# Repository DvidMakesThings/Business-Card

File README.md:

# Business_Card_LA Project

Business_Card_LA is a unique project where a business card doubles as a logic analyzer. It is designed based on Cypress CY7C68013A USB controller. It can sample 8 channels at the same time. The maximum sampling rate of each channel is 24Mhz, and the maximum logical level supports 5.5V. The software adopts sigrok-PulseView, which is open source, and supports Linux, Windows, Mac OS X and other platforms. It supports more than 100 kinds of protocol analysis, and can add its own protocol analysis.

## Specifications
- **Sampling rate and number of channels**: 24Mhz, 8 Channel
- **Signal input range**: 0-5.5V
- **High and low level recognition range**: Vin High: >2V, Vin Low: <0.8V
- **Communication mode**: USB 2.0 (In order to ensure the sampling rate of 24Mhz, try not to use USB docking station)

## Usage
1. **Download sigrok-PulseView Software**: Be sure to download the Release build from [sigrok Downloads](https://sigrok.org/wiki/Downloads).
2. **Install sigrok-PulseView & LogicAnalyzer driver**:
   - After PulseView is installed, run Zadig from the installation folder: `\sigrok\PulseView\zadig.exe`.
   - Select the device you want to install the driver on. The business card appears as Unknown device with VID/PID 04B4:8613.
   - Check Edit, change the device name to fx2LAFw, and then click Install Driver.
3. **Run PulseView**:
   - Click PulseView to run the software.
   - The status LED will light up and it's blue, indicating that the firmware is loaded successfully and the logic signal can be sampled.

## Supported Protocols
See [sigrok Supported Protocol decoders](https://sigrok.org/wiki/Protocol_decoders).

## License
This project is licensed under the GPL-3.0 License.

## Contact
For any questions or feedback, please contact:
- Email: [s.dvid@hotmail.com](mailto:s.dvid@hotmail.com)
- GitHub: [DvidMakesThings](https://github.com/DvidMakesThings)

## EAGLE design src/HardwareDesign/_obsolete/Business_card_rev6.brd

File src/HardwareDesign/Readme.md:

# # Business_Card_LA Project Hardware Design Files

## Contents
This folder contains the hardware design files for the Business_Card_LA project. The main components include:
- Schematic diagrams
- PCB layouts
- Bill of Materials (BOM)
- Gerber files

## Usage
To use these hardware design files:
1. Open the schematic diagrams and PCB layouts using EAGLE software.
2. Review the Bill of Materials for required components.
3. Follow the design files to assemble and test the hardware.
4. Use the Gerber files for PCB manufacturing.

## License
This project is licensed under the MIT License.

## Contact
For any questions or feedback, please contact:
- Email: [s.dvid@hotmail.com](mailto:s.dvid@hotmail.com)
- GitHub: [DvidMakesThings](https://github.com/DvidMakesThings)

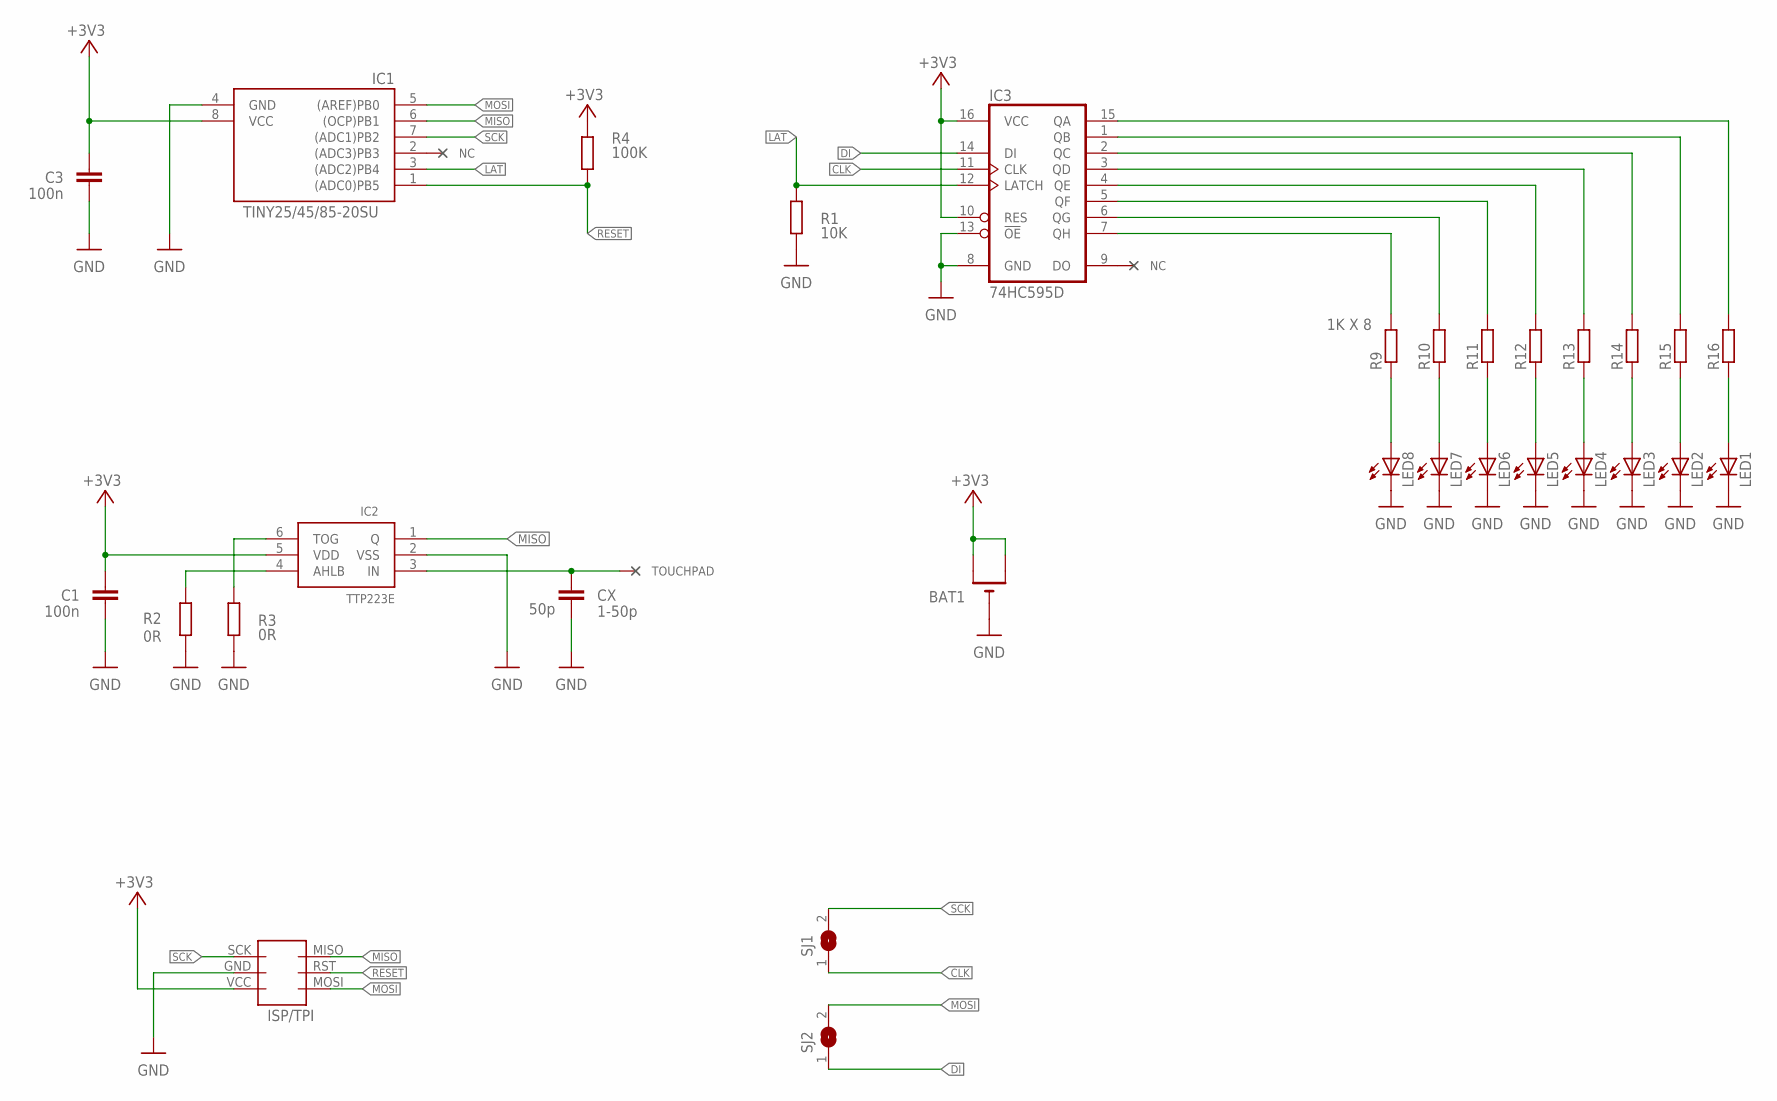
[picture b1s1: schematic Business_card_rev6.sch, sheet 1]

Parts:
BAT1: CR2032SMT; CR2032-SMD
C1, C3: 100n; C1206K
CX: 1-50p; C1206K
IC1: TINY25/45/85-20SU; SOIC8
IC2: TTP223E; SOT23-6
IC3: 74HC595D; SO16
LED1, LED2, LED3, LED4, LED5, LED6, LED7, LED8: LEDCHIPLED_0805; CHIPLED_0805
R1: 10K; M0805
R2, R3: 0R; M0805
R4: 100K; M0805
R9, R10, R11, R12, R13, R14, R15, R16: R-EU_M0805; M0805
SJ1, SJ2: SJ
U$11: AVR-ISP-6-EDGE; 6PAD_ISP

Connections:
+3V3: BAT1.+$1 (+), BAT1.+$2 (+1), C1.2, C3.2, IC1.8 (VCC), IC2.5 (VDD), IC3.10 (RES), IC3.16 (VCC), R4.2, U$11.VCC; also elsewhere on the board
CAPSEN: CX.2, IC2.3 (IN)
CLK: IC3.11 (CLK), SJ1.1
DI: IC3.14 (DI), SJ2.1
GND: BAT1.-, C1.1, C3.1, CX.1, IC1.4 (GND), IC2.2 (VSS), IC3.8 (GND), IC3.13 (!OE), LED1.C, LED2.C, LED3.C, LED4.C, LED5.C, LED6.C, LED7.C, LED8.C, R1.2, R2.1, R3.1, U$11.GND; also elsewhere on the board
LAT: IC1.3 ((ADC2)PB4), IC3.12 (LATCH), R1.1
MISO: IC1.6 ((OCP)PB1), IC2.1 (Q), U$11.MISO
MOSI: IC1.5 ((AREF)PB0), SJ2.2, U$11.MOSI
unnamed: IC3.15 (QA), R16.2
unnamed: IC3.1 (QB), R15.2
unnamed: IC2.6 (TOG), R3.2
unnamed: IC2.4 (AHLB), R2.2
unnamed: IC3.2 (QC), R14.2
unnamed: IC3.3 (QD), R13.2
unnamed: IC3.4 (QE), R12.2
unnamed: IC3.5 (QF), R11.2
unnamed: IC3.6 (QG), R10.2
unnamed: IC3.7 (QH), R9.2
unnamed: LED8.A, R9.1
unnamed: LED7.A, R10.1
unnamed: LED6.A, R11.1
unnamed: LED5.A, R12.1
unnamed: LED4.A, R13.1
unnamed: LED3.A, R14.1
unnamed: LED2.A, R15.1
unnamed: LED1.A, R16.1
RESET: IC1.1 ((ADC0)PB5), R4.1, U$11.RST
SCK: IC1.7 ((ADC1)PB2), SJ1.2, U$11.SCK

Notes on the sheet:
50p
TOUCHPAD
IC2
TTP223E
1K X 8

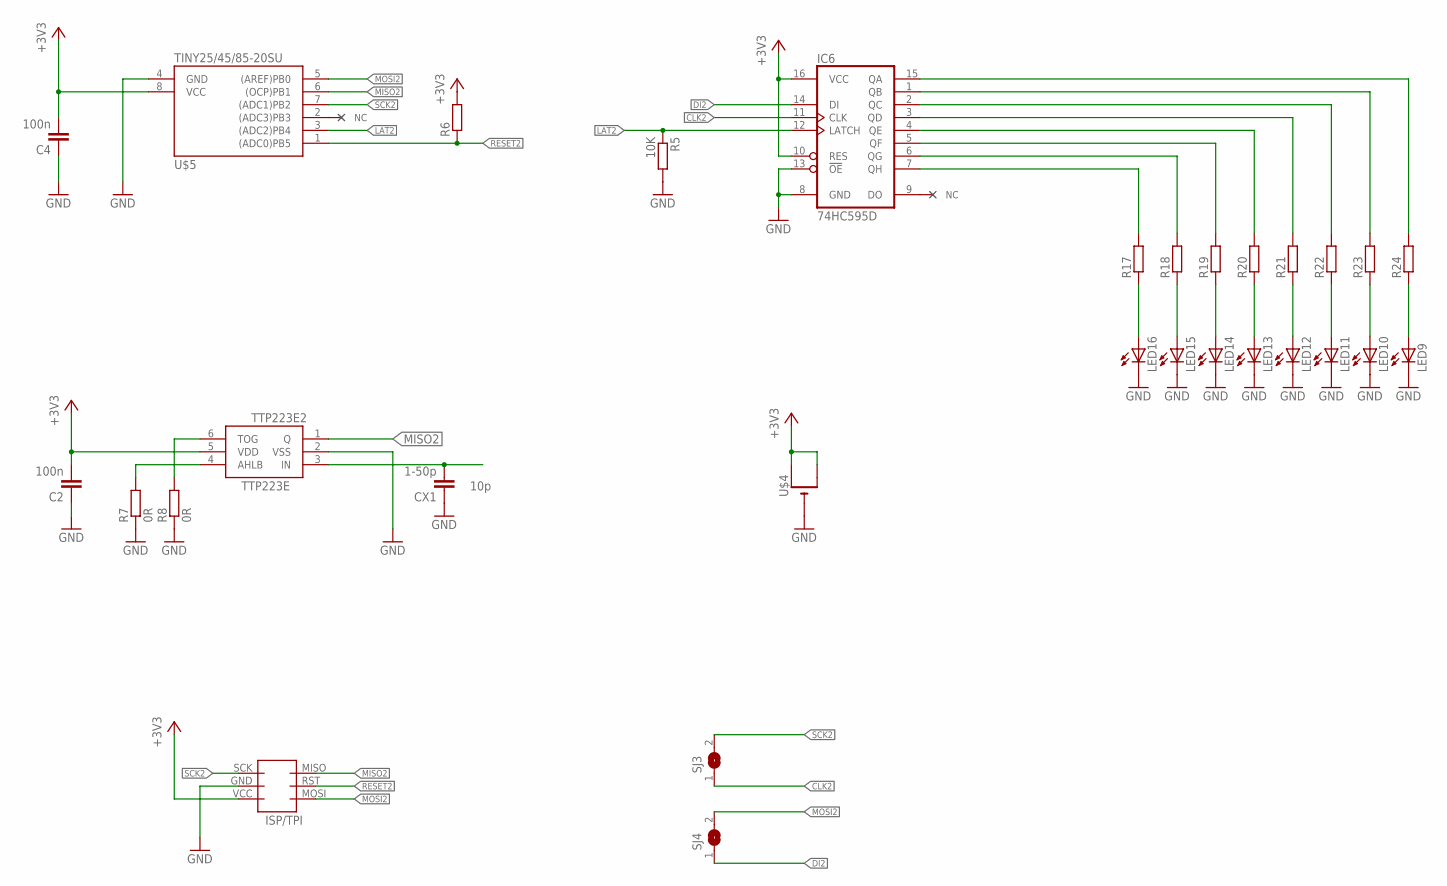
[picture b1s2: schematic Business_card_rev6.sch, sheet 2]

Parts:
C2, C4: 100n; C1206K
CX1: 1-50p; C1206K
IC6: 74HC595D; SO16
LED9, LED10, LED11, LED12, LED13, LED14, LED15, LED16: LEDCHIPLED_0805; CHIPLED_0805
R5: 10K; M0805
R6, R17, R18, R19, R20, R21, R22, R23, R24: R-EU_M0805; M0805
R7, R8: 0R; M0805
SJ3, SJ4: SJ
TTP223E2: TTP223E; SOT23-6
U$4: CR2032SMT; CR2032-SMD
U$5: TINY25/45/85-20SU; SOIC8
U$12: AVR-ISP-6-EDGE; 6PAD_ISP

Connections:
+3V3: C2.2, C4.2, IC6.10 (RES), IC6.16 (VCC), R6.2, TTP223E2.5 (VDD), U$4.+$1 (+), U$4.+$2 (+1), U$5.8 (VCC), U$12.VCC; also elsewhere on the board
CAPSEN1: CX1.2, TTP223E2.3 (IN)
CLK2: IC6.11 (CLK), SJ3.1
DI2: IC6.14 (DI), SJ4.1
GND: C2.1, C4.1, CX1.1, IC6.8 (GND), IC6.13 (!OE), LED9.C, LED10.C, LED11.C, LED12.C, LED13.C, LED14.C, LED15.C, LED16.C, R5.2, R7.1, R8.1, TTP223E2.2 (VSS), U$4.-, U$5.4 (GND), U$12.GND; also elsewhere on the board
LAT2: IC6.12 (LATCH), R5.1, U$5.3 ((ADC2)PB4)
MISO2: TTP223E2.1 (Q), U$5.6 ((OCP)PB1), U$12.MISO
MOSI2: SJ4.2, U$5.5 ((AREF)PB0), U$12.MOSI
unnamed: R8.2, TTP223E2.6 (TOG)
unnamed: R7.2, TTP223E2.4 (AHLB)
unnamed: IC6.15 (QA), R24.2
unnamed: IC6.1 (QB), R23.2
unnamed: IC6.2 (QC), R22.2
unnamed: IC6.3 (QD), R21.2
unnamed: IC6.4 (QE), R20.2
unnamed: IC6.5 (QF), R19.2
unnamed: IC6.6 (QG), R18.2
unnamed: IC6.7 (QH), R17.2
unnamed: LED16.A, R17.1
unnamed: LED15.A, R18.1
unnamed: LED14.A, R19.1
unnamed: LED13.A, R20.1
unnamed: LED12.A, R21.1
unnamed: LED11.A, R22.1
unnamed: LED10.A, R23.1
unnamed: LED9.A, R24.1
RESET2: R6.1, U$5.1 ((ADC0)PB5), U$12.RST
SCK2: SJ3.2, U$5.7 ((ADC1)PB2), U$12.SCK

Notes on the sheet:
10p

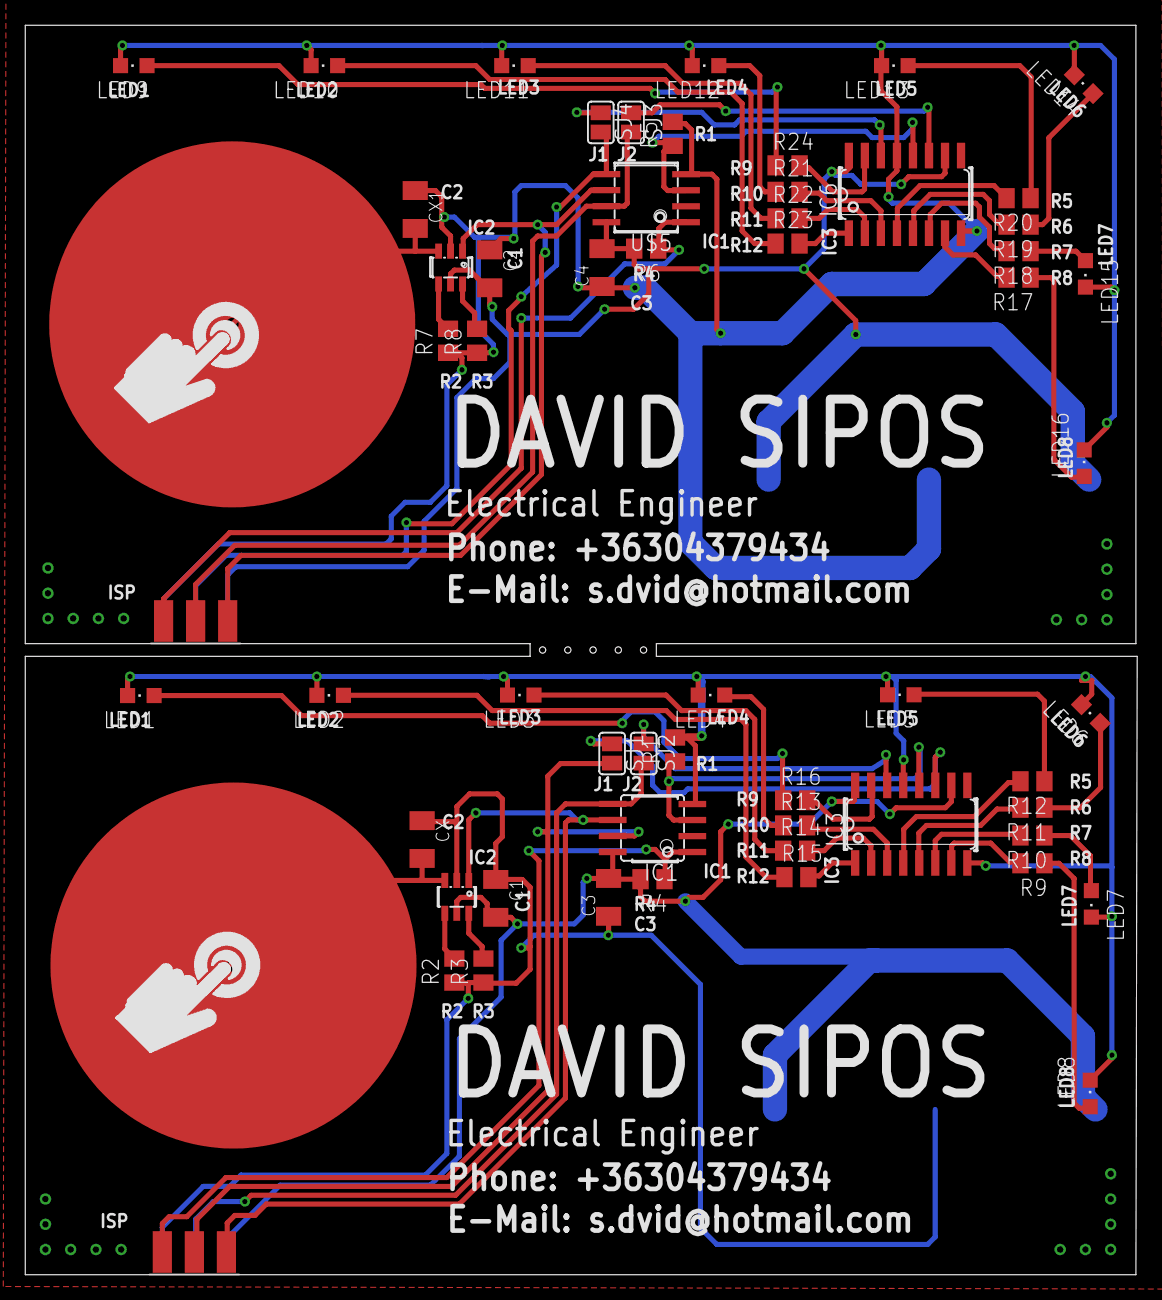
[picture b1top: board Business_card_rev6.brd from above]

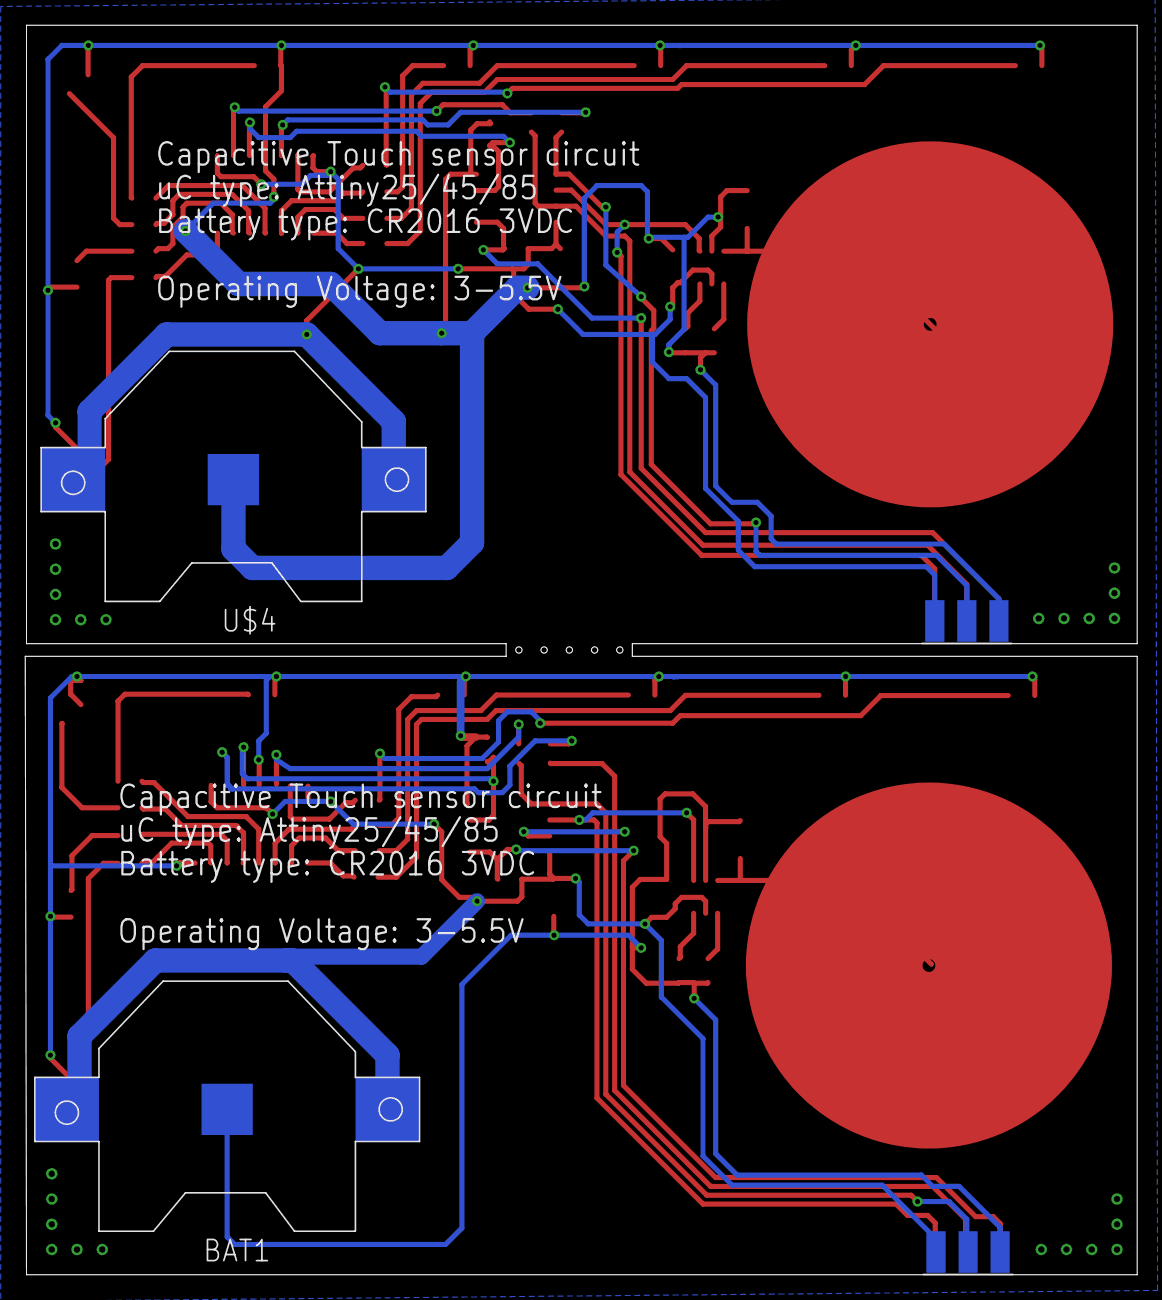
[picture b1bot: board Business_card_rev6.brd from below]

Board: 2 copper layers, 88.1 x 99.0 mm, 60 parts (2 on the bottom side), 54 nets.

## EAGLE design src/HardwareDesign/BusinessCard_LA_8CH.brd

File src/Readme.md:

# Business_Card_LA Project Design files

This repository contains source files for software and hardware designs related to the Business_Card_LA project.

## Contents

- **Software**: Source code for the software components.
- **Hardware**: Design files for the hardware components.

## Usage

1. Clone the repository.
2. Navigate to the `src` directory.
3. Follow the instructions in the respective subdirectories for software and hardware.

## License
This project is licensed under the MIT License.

## Contact
For any questions or feedback, please contact:
- Email: [s.dvid@hotmail.com](mailto:s.dvid@hotmail.com)
- GitHub: [DvidMakesThings](https://github.com/DvidMakesThings)

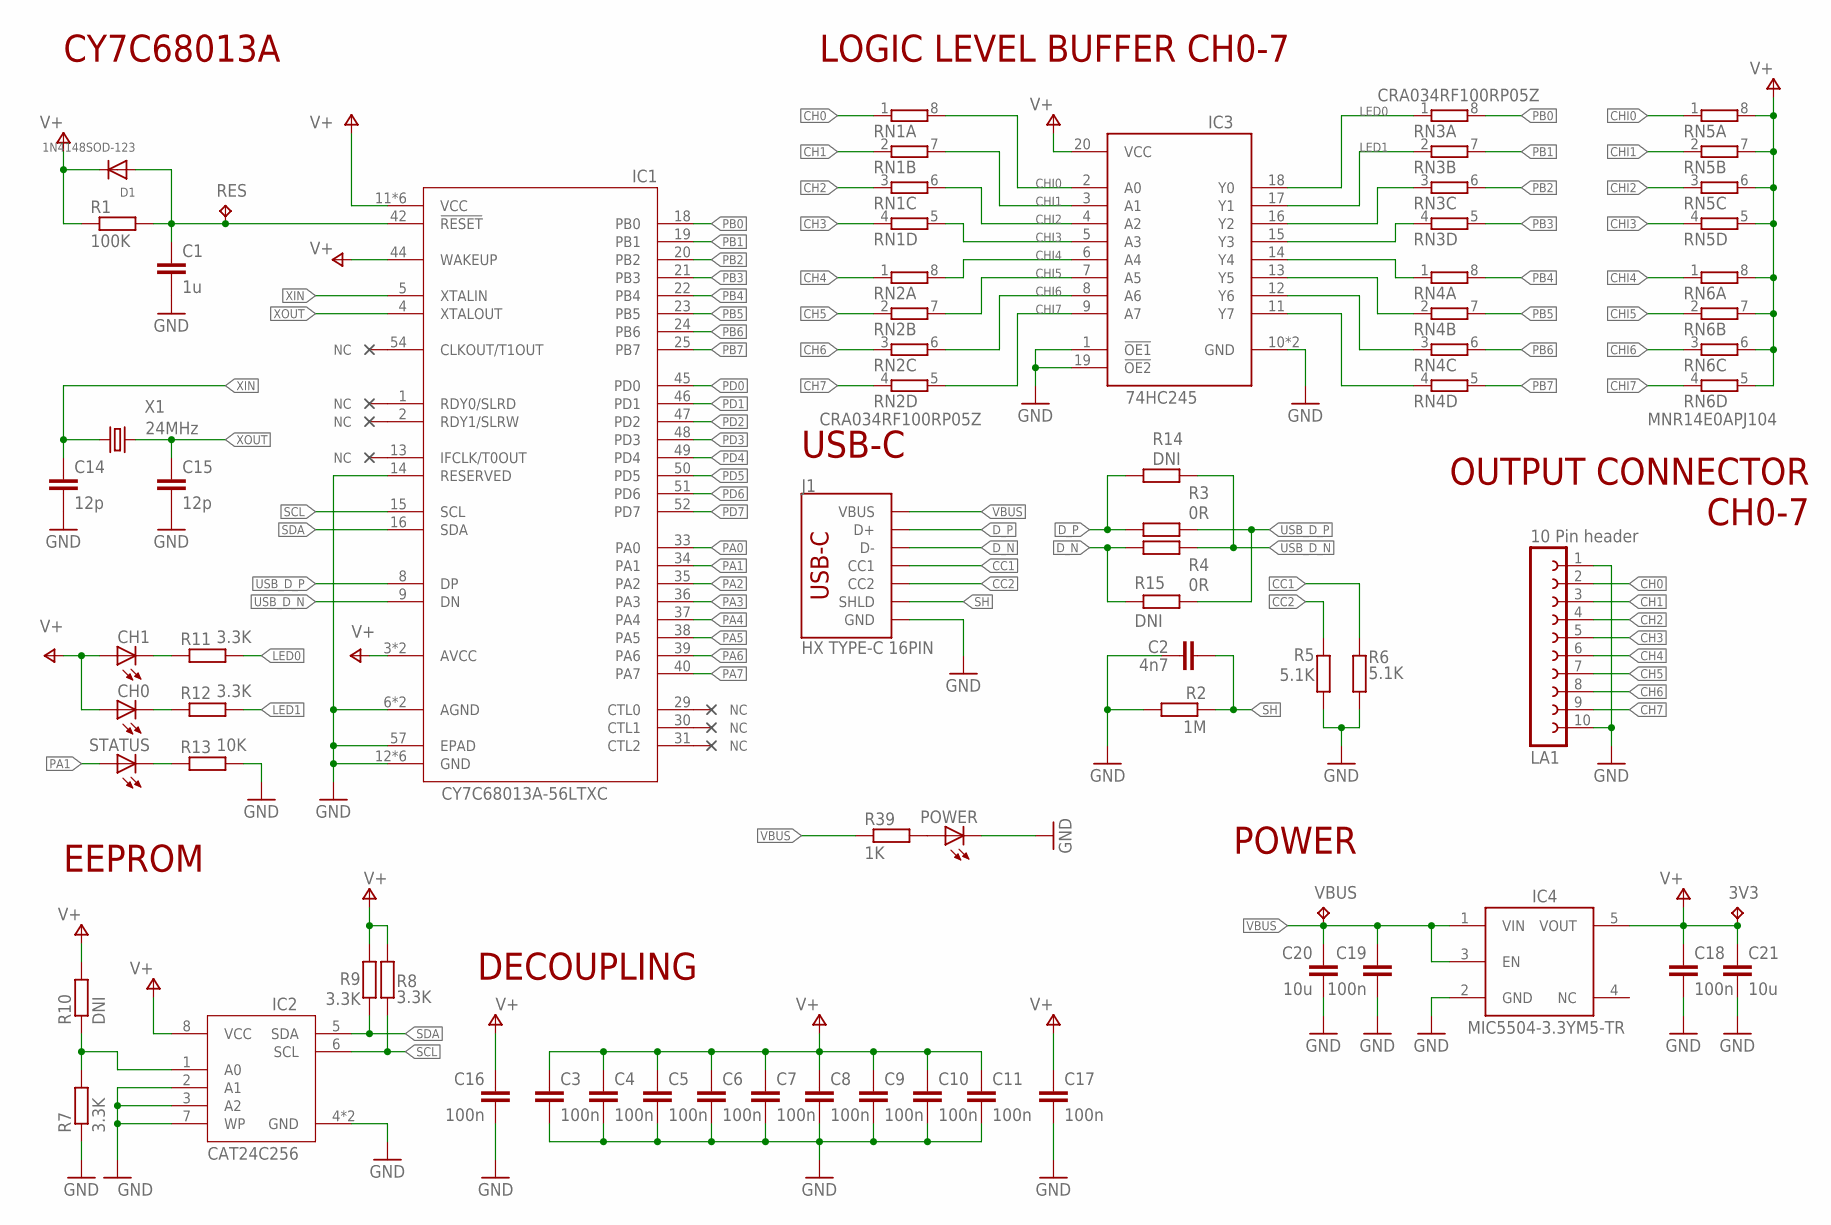
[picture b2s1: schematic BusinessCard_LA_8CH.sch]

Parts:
3V3: TPB1,27; B1,27
C1: 1u; C0402K
C2: 4n7; C0402K
C3, C4, C5, C6, C7, C8, C9, C10, C11, C16, C17, C18, C19: 100n; C0402K
C14, C15: 12p; C0402K
C20, C21: 10u; C0805K
CH0, CH1: 19-217/GHC-YR1S2/3T; CHIP-LED0603
D1: 1N4148SOD-123; SOD-123FL
IC1: CY7C68013A-56LTXC; QFN50P800X800X100-57T665
IC2: CAT24C256HU4IGT3; SON50P300X200X50-9T130X140N
IC3: SN74LVC541ARGYR; QFN50P350X450X100-25T305X205N
IC4: MIC5504-3.3YM5-TR; SOT23-5
J1: HX TYPE-C 16PIN; USB-C-16P-2LAYER-PADS
LA1: 10 Pin header; FE10
POWER: 19-213/Y2C-CQ2R2L/3T(CY); CHIP-LED0603
R1: 100K; R0402
R2: 1M; R0402
R3, R4: 0R; R0402
R5, R6: 5.1K; R0402
R7, R8, R9, R11, R12: 3.3K; R0402
R10, R14, R15: DNI; R0402
R13: 10K; R0402
R39: 1K; R0402
RES: TPB1,27; B1,27
RN1, RN2, RN3, RN4: CRA034RF100RP05Z; CAT16
RN5, RN6: MNR14E0APJ104; CAT16
STATUS: YLED0603B; CHIP-LED0603
VBUS: TPB1,27; B1,27
X1: 24MHz; 3.2X2.5_KX-7

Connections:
CC1: J1.A5 (CC1), R6.1
CC2: J1.B5 (CC2), R5.1
CH0: LA1.2, RN1.1
CH1: LA1.3, RN1.2 (1)
CH2: LA1.4, RN1.3 (1)
CH3: LA1.5, RN1.4 (1)
CH4: LA1.6, RN2.1
CH5: LA1.7, RN2.2 (1)
CH6: LA1.8, RN2.3 (1)
CH7: LA1.9, RN2.4 (1)
CHI0: IC3.2 (A0), RN1.8 (2), RN5.1
CHI1: IC3.3 (A1), RN1.7 (2), RN5.2 (1)
CHI2: IC3.4 (A2), RN1.6 (2), RN5.3 (1)
CHI3: IC3.5 (A3), RN1.5 (2), RN5.4 (1)
CHI4: IC3.6 (A4), RN2.8 (2), RN6.1
CHI5: IC3.7 (A5), RN2.7 (2), RN6.2 (1)
CHI6: IC3.8 (A6), RN2.6 (2), RN6.3 (1)
CHI7: IC3.9 (A7), RN2.5 (2), RN6.4 (1)
D_N: J1.A7 (D-), J1.B7 (D-), R4.2, R15.2
D_P: J1.A6 (D+), J1.B6 (D+), R3.2, R14.2
GND: C1.2, C2.2, C3.2, C4.2, C5.2, C6.2, C7.2, C8.2, C9.2, C10.2, C11.2, C14.2, C15.2, C16.2, C17.2, C18.2, C19.2, C20.2, C21.2, IC1.6 (AGND), IC1.10 (AGND), IC1.12 (GND), IC1.14 (RESERVED), IC1.26 (GND), IC1.28 (GND), IC1.41 (GND), IC1.53 (GND), IC1.56 (GND), IC1.57 (EPAD), IC2.2 (A1), IC2.3 (A2), IC2.4 (GND), IC2.7 (WP), IC2.9 (GND), IC3.1 (!OE1), IC3.10 (GND), IC3.19 (!OE2), IC3.PAD (GND), IC4.2 (GND), J1.GND, J1.GND2 (GND), LA1.1, LA1.10, POWER.C, R2.2, R5.2, R6.2, R7.1, R13.2
LED0: IC3.18 (Y0), R11.2, RN3.1
LED1: IC3.17 (Y1), R12.2, RN3.2 (1)
unnamed: IC2.1 (A0), R7.2, R10.1
unnamed: POWER.A, R39.2
unnamed: C1.1, D1.A, IC1.42 (!RESET), R1.2, RES.TP
unnamed: IC3.16 (Y2), RN3.3 (1)
unnamed: IC3.15 (Y3), RN3.4 (1)
unnamed: IC3.14 (Y4), RN4.1
unnamed: IC3.13 (Y5), RN4.2 (1)
unnamed: IC3.12 (Y6), RN4.3 (1)
unnamed: IC3.11 (Y7), RN4.4 (1)
unnamed: CH1.C, R11.1
unnamed: CH0.C, R12.1
unnamed: R13.1, STATUS.C
PA0: IC1.33 (PA0)
PA1: IC1.34 (PA1), STATUS.A
PA2: IC1.35 (PA2)
PA3: IC1.36 (PA3)
PA4: IC1.37 (PA4)
PA5: IC1.38 (PA5)
PA6: IC1.39 (PA6)
PA7: IC1.40 (PA7)
PB0: IC1.18 (PB0), RN3.8 (2)
PB1: IC1.19 (PB1), RN3.7 (2)
PB2: IC1.20 (PB2), RN3.6 (2)
PB3: IC1.21 (PB3), RN3.5 (2)
PB4: IC1.22 (PB4), RN4.8 (2)
PB5: IC1.23 (PB5), RN4.7 (2)
PB6: IC1.24 (PB6), RN4.6 (2)
PB7: IC1.25 (PB7), RN4.5 (2)
PD0: IC1.45 (PD0)
PD1: IC1.46 (PD1)
PD2: IC1.47 (PD2)
PD3: IC1.48 (PD3)
PD4: IC1.49 (PD4)
PD5: IC1.50 (PD5)
PD6: IC1.51 (PD6)
PD7: IC1.52 (PD7)
SCL: IC1.15 (SCL), IC2.6 (SCL), R8.1
SDA: IC1.16 (SDA), IC2.5 (SDA), R9.1
SH: C2.1, J1.SHLD1 (SHLD), J1.SHLD2 (SHLD), J1.SHLD3 (SHLD), J1.SHLD4 (SHLD), R2.1
USB_D_N: IC1.9 (DN), R4.1, R14.1
USB_D_P: IC1.8 (DP), R3.1, R15.1
V+: 3V3.TP, C3.1, C4.1, C5.1, C6.1, C7.1, C8.1, C9.1, C10.1, C11.1, C16.1, C17.1, C18.1, C21.1, CH0.A, CH1.A, D1.C, IC1.3 (AVCC), IC1.7 (AVCC), IC1.11 (VCC), IC1.17 (VCC), IC1.27 (VCC), IC1.32 (VCC), IC1.43 (VCC), IC1.44 (WAKEUP), IC1.55 (VCC), IC2.8 (VCC), IC3.20 (VCC), IC4.5 (VOUT), R1.1, R8.2, R9.2, R10.2, RN5.5 (2), RN5.6 (2), RN5.7 (2), RN5.8 (2), RN6.5 (2), RN6.6 (2), RN6.7 (2), RN6.8 (2)
VBUS: C19.1, C20.1, IC4.1 (VIN), IC4.3 (EN), J1.VBUS1 (VBUS), J1.VBUS2 (VBUS), R39.1, VBUS.TP
XIN: C14.1, IC1.5 (XTALIN), X1.1
XOUT: C15.1, IC1.4 (XTALOUT), X1.3 (2)

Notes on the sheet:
USB-C
CY7C68013A
EEPROM
OUTPUT CONNECTOR CH0-7
POWER
LOGIC LEVEL BUFFER CH0-7
DECOUPLING

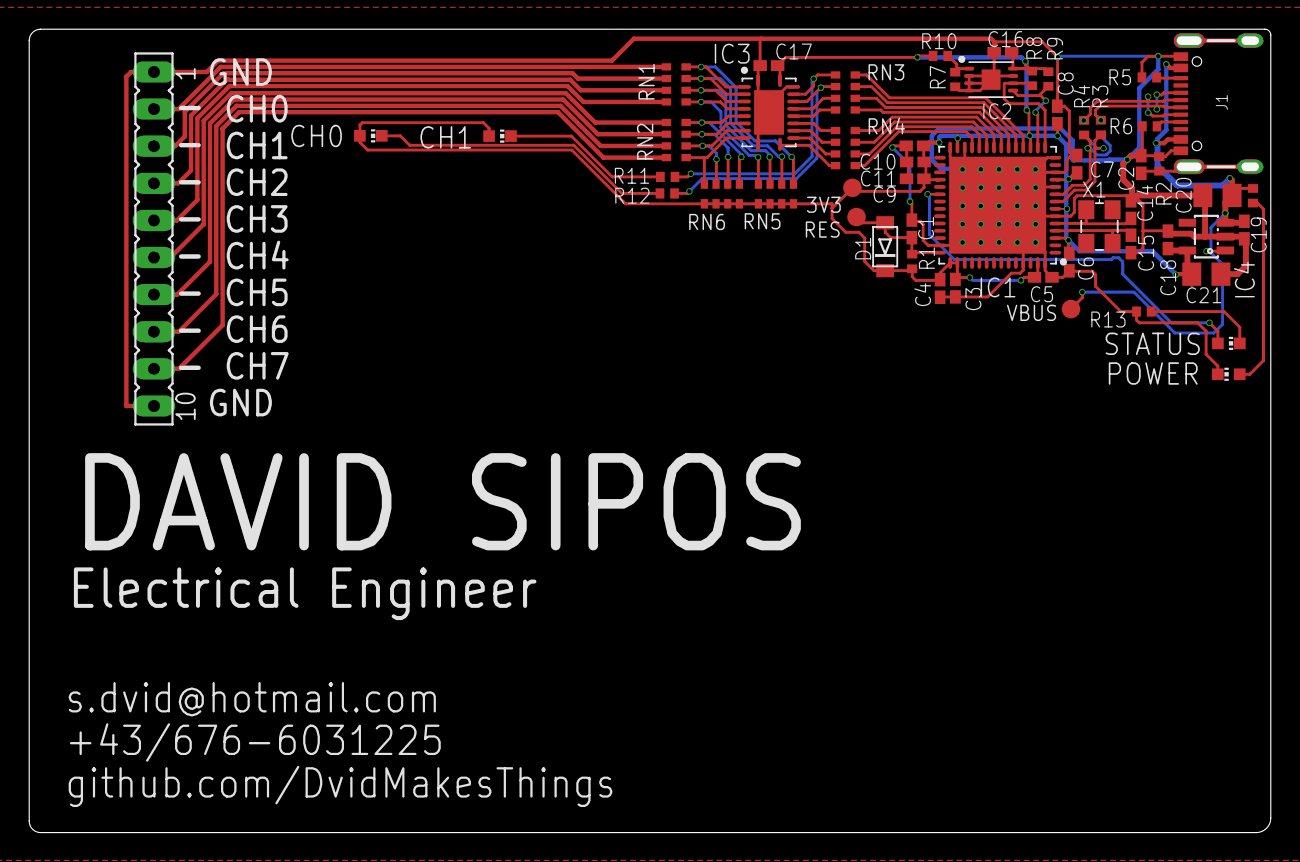
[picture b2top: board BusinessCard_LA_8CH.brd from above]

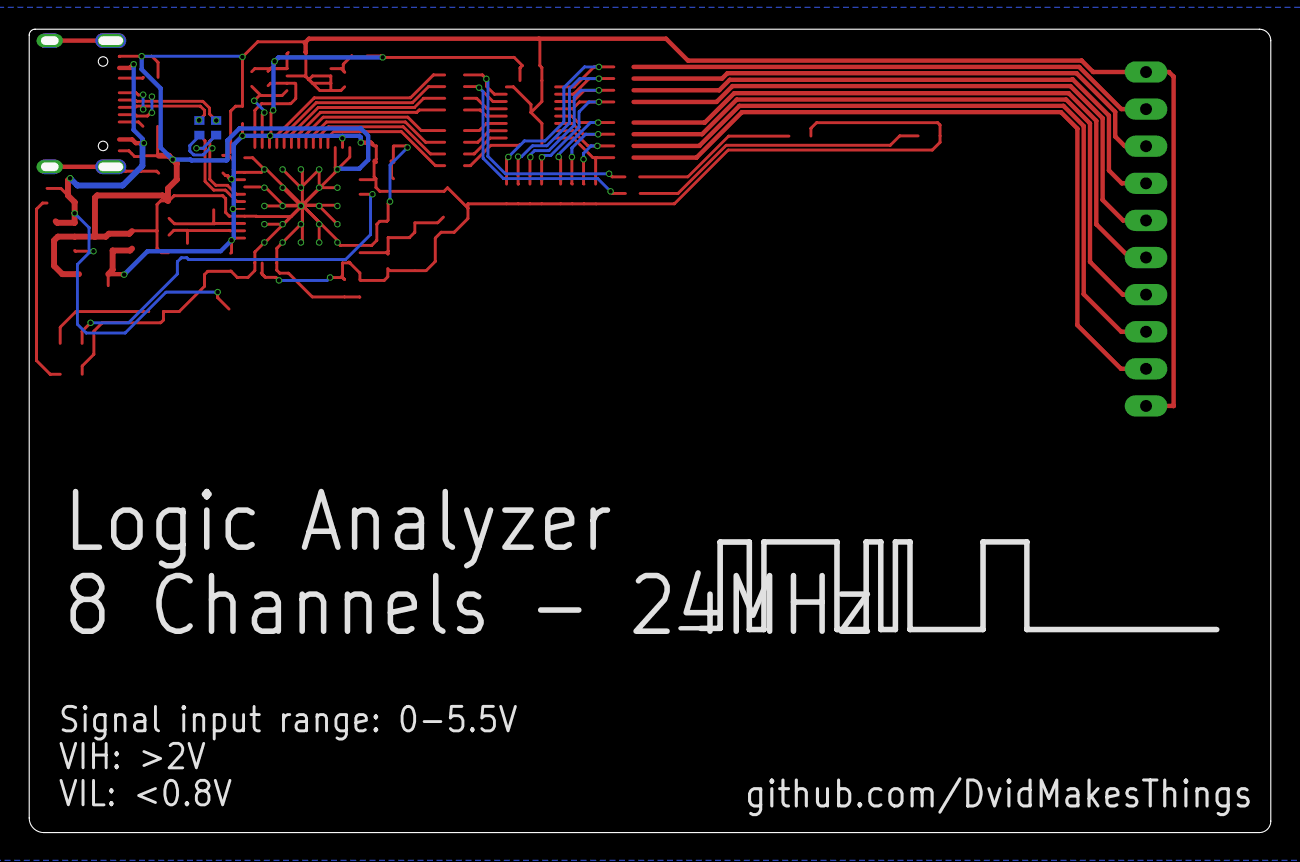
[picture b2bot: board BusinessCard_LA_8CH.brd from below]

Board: 2 copper layers, 84.4 x 54.4 mm, 56 parts (2 on the bottom side), 53 nets.

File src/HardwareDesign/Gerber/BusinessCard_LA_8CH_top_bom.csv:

Comment,Designator,Footprint,LCSC Part #
,POWER,CHIP-LED0603,
0R,R3 R4,R0402,
1K,R39,R0402,
1M,R2,R0402,
1N4148SOD-123,D1,SOD-123FL,
1u,C1,C0402K,
3.3K,R7 R8 R9 R11 R12,R0402,
4n7,C2,C0402K,
5.1K,R5 R6,R0402,
10K,R13,R0402,
10u,C20 C21,C0805K,
12p,C14 C15,C0402K,
19-217/GHC-YR1S2/3T,CH0 CH1,CHIP-LED0603,
24MHz,X1,3.2X2.5_KX-7,
100K,R1,R0402,
100n,C3 C4 C5 C6 C7 C8 C9 C10 C11 C16 C17 C18 C19,C0402K,
CAT24C256HU4IGT3,IC2,SON50P300X200X50-9T130X140N,
CRA034RF100RP05Z,RN1 RN2 RN3 RN4,CAT16,
CY7C68013A-56LTXC,IC1,QFN50P800X800X100-57T665,
DNI,R10,R0402,
HX TYPE-C 16PIN,J1,USB-C-16P-2LAYER-PADS,
MIC5504-3.3YM5-TR,IC4,SOT23-5,
MNR14E0APJ104,RN5 RN6,CAT16,
SN74LVC541ARGYR,IC3,QFN50P350X450X100-25T305X205N,
TPB1 27,3V3,B1 27,
TPB1 27,RES,B1 27,
TPB1 27,VBUS,B1 27,
YLED0603B,STATUS,CHIP-LED0603,

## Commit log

2024-11-29 initial creation
2024-11-29 add LICENSE

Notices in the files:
parts and their libraries:
crystal-geyer_V1_0: Copyright: Geyer-Electronic
SparkFun-Connectors: Licensing: Creative Commons ShareAlike 4.0 International - https://creativecommons.org/licenses/by-sa/4.0
